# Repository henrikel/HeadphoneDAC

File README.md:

# HeadphoneDAC
This project started with the purchase of a couple of Chinese DAC modules designed around a PCM1794 DAC from TI. It turned out the DAC module was of quite good quality with genuine parts and a design closely following the datasheet reference design for the analog part. I therefore decided to make a headphone amplifier out of this with USB input. For this reason I had to design and construct the actual headphone amplifier as well as the logic that converts the USB data into an I2S stream that can be read by the DAC. A suitable power supply also had to be designed. All in all, the whole project therefore consists of 4 modules, one logic board with a STM32F411 running the show, one DAC module, one headphone amplifier module and one power supply.

The logic module takes care of converting the USB audio stream into I2S data on a USB full-speed interface. This sets a limit of the maximum sample rate to 96 kHz. It implements the proper way to handle the audio data, i.e., asynchronously. As of now, the system clock of the STM32 microcontroller is used for the audio clock, something that can be improved in the future. The STM32F411 microcontroller also takes care of the user interface, which consists of a few buttons and LEDs to indicate playback, mute and sampling rate. A LED VU meter is also implemented as well as control of a relay to avoid pops and clicks at startup and shutdown.

The headphone amplifier is a class A output design, using a NE5534 opamp as voltage amplifier and an emitter follower implemented as a Sziklai pair with a current sink. The design itself has borrowed from two sources, the Youtube channel Innove Workshop (but modified for dual supply) and Elliott Sound Products (https://sound-au.com/project113.htm). It is a relatively simple design, but measures well (I get THD figures of approximately 0.03% at 1 kHz and 100 mW, which is around the limit of my home made sound card using a Raspberry Pi and Hifiberry ADC+DAC). 

The power supply is a simple design giving +/-12 V and +5V, with a toroidal transformer and LM317/337 and L7812/7809/7805.

I am pretty happy with this build and think it sounds really good with my Beyerdynamic DT880 Pro headphones (250 ohms). I had some problems with ground loops and interference from the transformer in the case I built for the amplifier, but I think I have sorted out most of that now with some tweaking of the orientation of the transformer as well as appropriate grounding. What remains is an irritating high-pitched interference obviously coming from the digital parts of the controller module, which oddly enough can only be heard when muting the sound (if streaming is on, but no music is playing or very low levels of music, I can't hear it).

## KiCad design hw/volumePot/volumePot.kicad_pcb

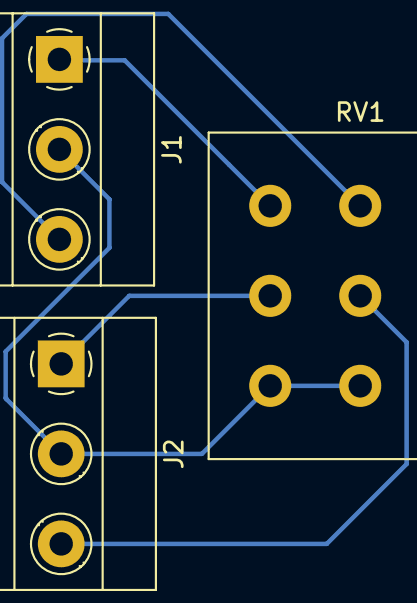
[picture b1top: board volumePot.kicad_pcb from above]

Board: 2 copper layers, 3 parts (0 on the bottom side), 5 nets.

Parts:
J1, J2: Screw_Terminal_01x03; TerminalBlock_Phoenix_MKDS-1,5-3_1x03_P5.00mm_Horizontal
RV1: R_POT_Dual; Potentiometer_Alps_RK163_Dual_Horizontal

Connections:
unnamed: J1.1, RV1.6
unnamed: J1.2, J2.2, RV1.1, RV1.4
unnamed: J1.3, RV1.3
unnamed: J2.1, RV1.5
unnamed: J2.3, RV1.2

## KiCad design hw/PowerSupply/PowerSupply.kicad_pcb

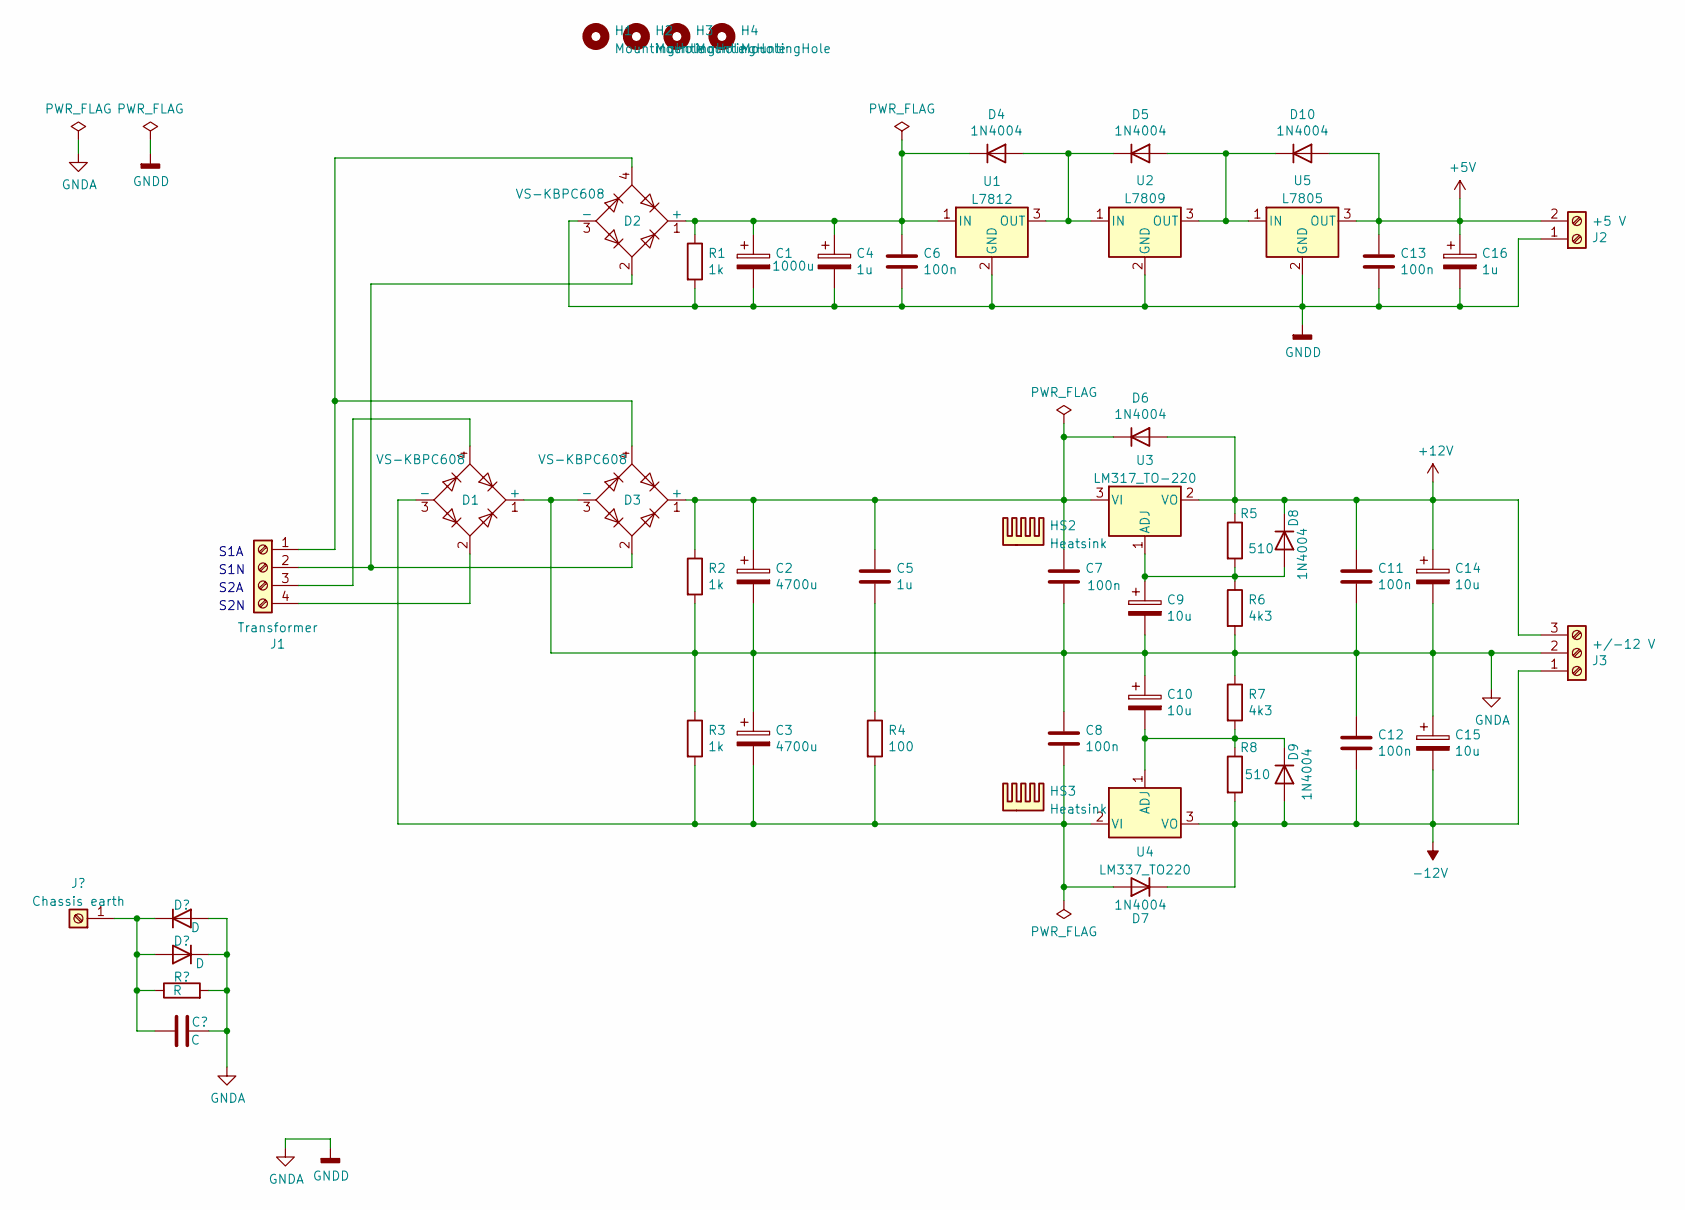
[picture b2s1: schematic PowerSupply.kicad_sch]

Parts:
C1: 1000u; CP_Radial_D18.0mm_P7.50mm
C2, C3: 4700u; CP_Radial_D18.0mm_P7.50mm
C4, C16: 1u; CP_Radial_D5.0mm_P2.00mm
C5: 1u; C_Rect_L7.0mm_W2.5mm_P5.00mm
C6, C7, C8, C11, C12, C13: 100n; C_Rect_L7.0mm_W2.5mm_P5.00mm
C9, C10, C14, C15: 10u; CP_Radial_D5.0mm_P2.00mm
D1, D2, D3: VS-KBPC608; Diode_Bridge_Vishay_KBPC6
D4, D5, D6, D7, D8, D9, D10: 1N4004; D_DO-41_SOD81_P10.16mm_Horizontal
H1, H2, H3, H4: MountingHole; MountingHole_3.2mm_M3
HS2, HS3: Heatsink; Heatsink_Fischer_SK104-STC-STIC_35x13mm_2xDrill2.5mm
J1: Transformer; TerminalBlock_Phoenix_MKDS-1,5-4_1x04_P5.00mm_Horizontal
J2: +5 V; TerminalBlock_Phoenix_MKDS-1,5-2_1x02_P5.00mm_Horizontal
J3: +/-12 V; TerminalBlock_Phoenix_MKDS-1,5-3_1x03_P5.00mm_Horizontal
R1, R2, R3: 1k; R_Axial_DIN0414_L11.9mm_D4.5mm_P20.32mm_Horizontal
R4: 100; R_Axial_DIN0207_L6.3mm_D2.5mm_P10.16mm_Horizontal
R5, R8: 510; R_Axial_DIN0207_L6.3mm_D2.5mm_P10.16mm_Horizontal
R6, R7: 4k3; R_Axial_DIN0207_L6.3mm_D2.5mm_P10.16mm_Horizontal
U1: L7812; TO-220-3_Vertical
U2: L7809; TO-220-3_Vertical
U3: LM317_TO-220; TO-220-3_Vertical
U4: LM337_TO220; TO-220-3_Vertical
U5: L7805; TO-220-3_Vertical

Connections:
+5V: C13.1, C16.1, D10.2 (A), J2.2, U5.3 (OUT)
+12V: C11.1, C14.1, D6.2 (A), D8.1 (K), J3.3, R5.1, U3.2 (VO)
-12V: C12.2, C15.2, D7.1 (K), D9.2 (A), J3.1, R8.2, U4.3 (VO)
GNDA: C1.2, C2.2, C3.1, C4.2, C6.2, C7.2, C8.1, C9.2, C10.1, C11.2, C12.1, C13.2, C14.2, C15.1, C16.2, D1.1 (+), D2.3 (-), D3.3 (-), J2.1, J3.2, R1.2, R2.2, R3.1, R6.2, R7.1, U1.2 (GND), U2.2 (GND), U5.2 (GND)
unnamed: C1.1, C4.1, C6.1, D2.1 (+), D4.1 (K), R1.1, U1.1 (IN)
unnamed: C2.1, C5.1, C7.1, D3.1 (+), D6.1 (K), R2.1, U3.3 (VI)
unnamed: C3.2, C8.2, D1.3 (-), D7.2 (A), R3.2, R4.2, U4.2 (VI)
unnamed: C5.2, R4.1
unnamed: C9.1, D8.2 (A), R5.2, R6.1, U3.1 (ADJ)
unnamed: C10.2, D9.1 (K), R7.2, R8.1, U4.1 (ADJ)
unnamed: D1.2, J1.4
unnamed: D1.4, J1.3
unnamed: D2.2, D3.2, J1.2
unnamed: D2.4, D3.4, J1.1
unnamed: D4.2 (A), D5.1 (K), U1.3 (OUT), U2.1 (IN)
unnamed: D5.2 (A), D10.1 (K), U2.3 (OUT), U5.1 (IN)

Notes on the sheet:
S1N
S2N
S2A
S1A

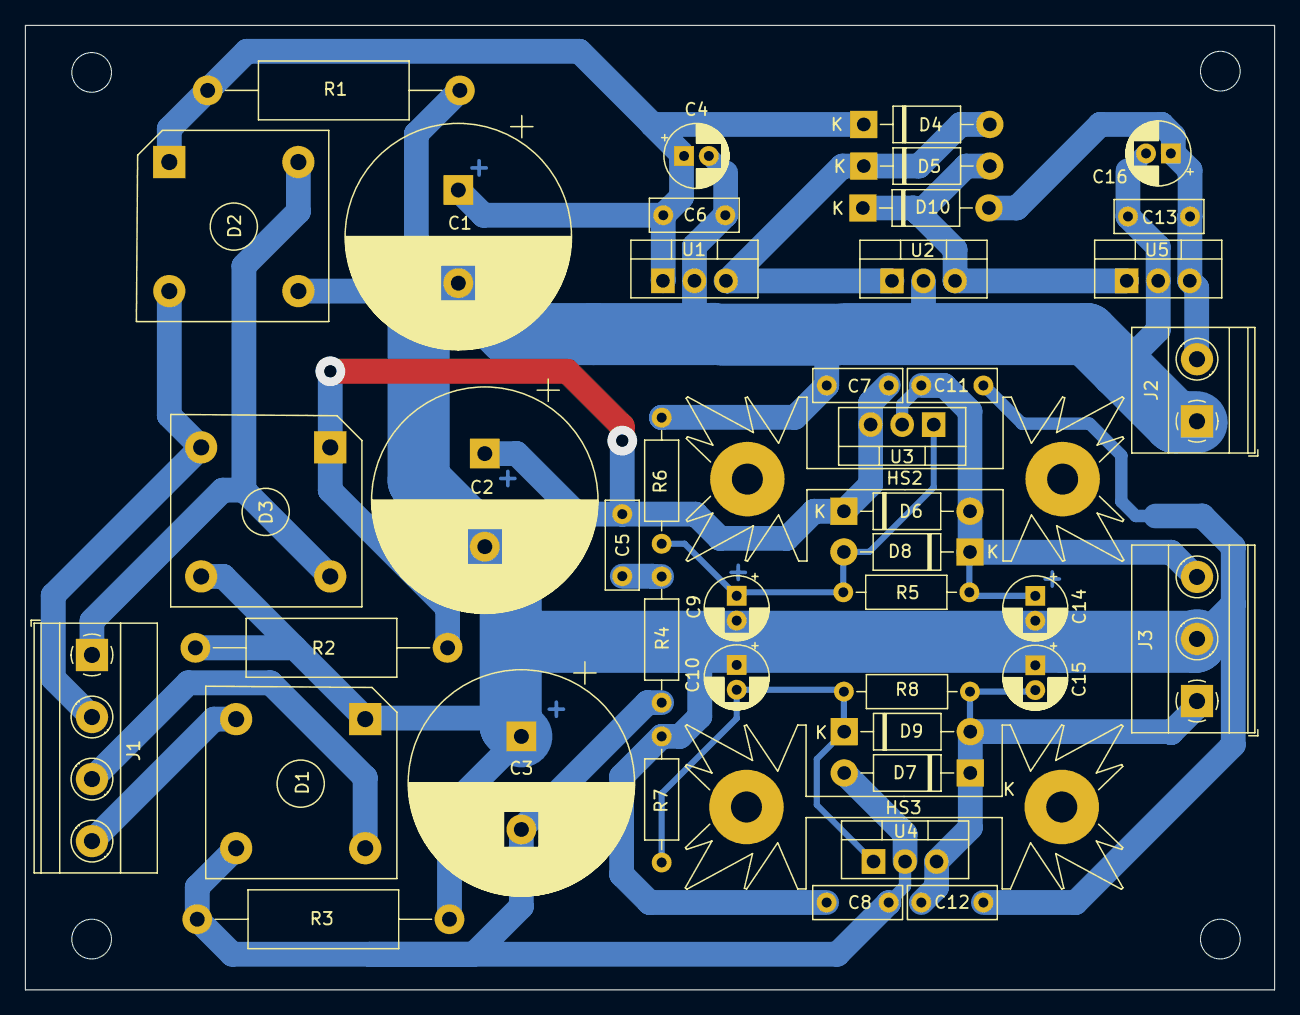
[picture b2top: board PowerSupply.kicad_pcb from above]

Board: 2 copper layers, 100.6 x 77.7 mm, 48 parts (0 on the bottom side), 16 nets.

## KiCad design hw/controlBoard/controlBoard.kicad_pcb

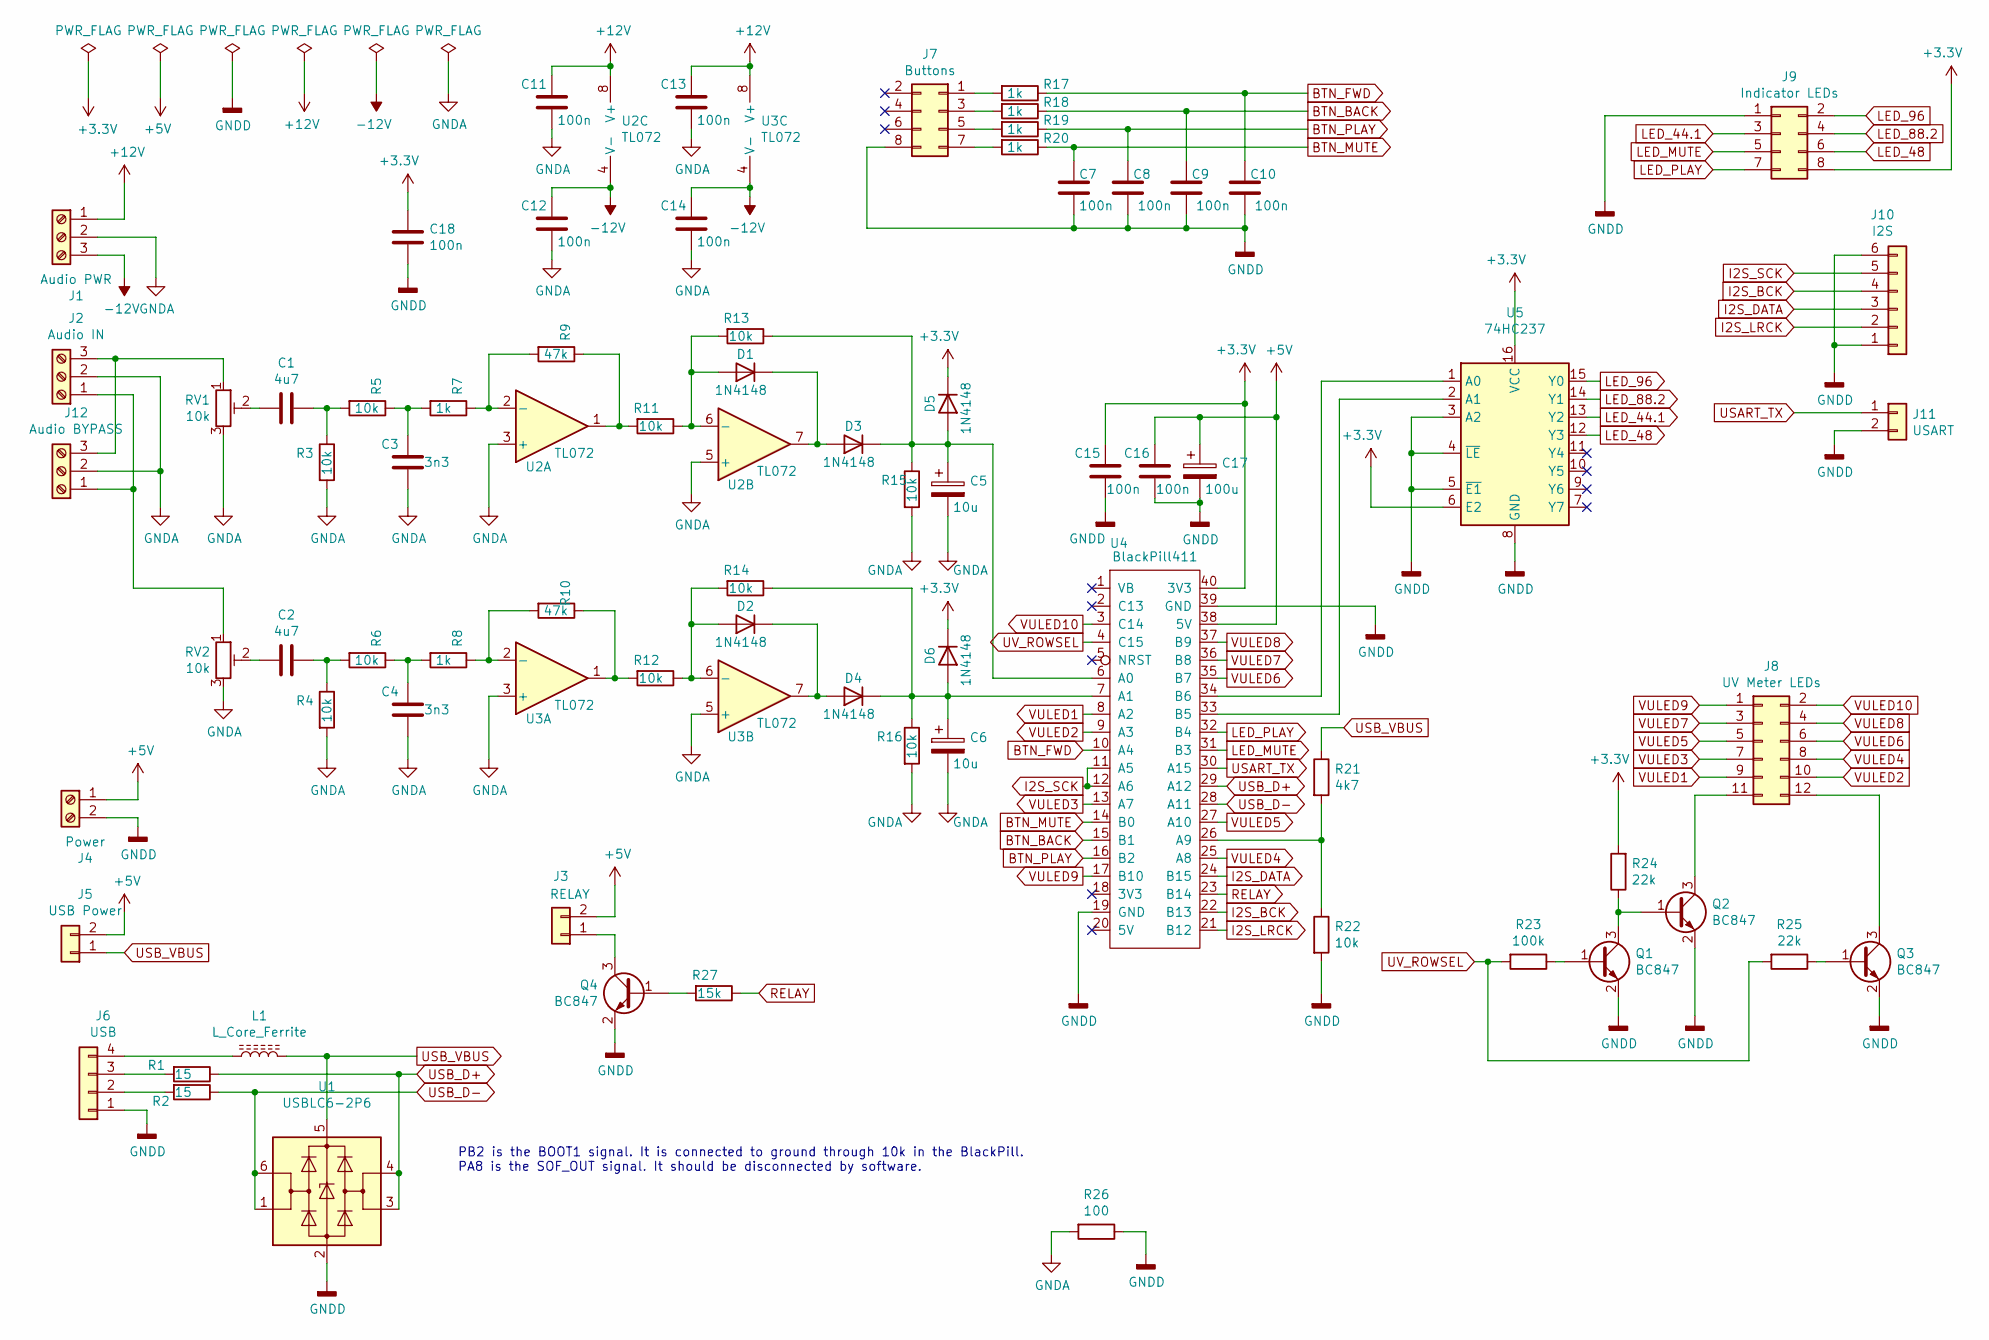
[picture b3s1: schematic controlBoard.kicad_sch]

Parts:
C1, C2: 4u7; C_0805_2012Metric_Pad1.18x1.45mm_HandSolder
C3, C4: 3n3; C_0805_2012Metric_Pad1.18x1.45mm_HandSolder
C5, C6: 10u; C_0805_2012Metric_Pad1.18x1.45mm_HandSolder
C7, C8, C9, C10, C11, C12, C13, C14, C15, C16, C18: 100n; C_0805_2012Metric_Pad1.18x1.45mm_HandSolder
C17: 100u; CP_Elec_6.3x5.4
D1, D2, D3, D4, D5, D6: 1N4148; D_SOD-323_HandSoldering
J1: Audio PWR; TerminalBlock_bornier-3_P5.08mm
J2: Audio IN; TerminalBlock_bornier-3_P5.08mm
J3: RELAY; PinHeader_1x02_P2.54mm_Vertical
J4: Power; TerminalBlock_bornier-2_P5.08mm
J5: USB Power; PinHeader_1x02_P2.54mm_Vertical
J6: USB; PinHeader_1x04_P2.54mm_Vertical
J7: Buttons; PinHeader_2x04_P2.54mm_Vertical
J8: UV Meter LEDs; PinHeader_2x06_P2.54mm_Vertical
J9: Indicator LEDs; PinHeader_2x04_P2.54mm_Vertical
J10: I2S; PinHeader_1x06_P2.54mm_Vertical
J11: USART; PinHeader_1x02_P2.54mm_Vertical
J12: Audio BYPASS; TerminalBlock_bornier-3_P5.08mm
L1: L_Core_Ferrite; L_Axial_L13.0mm_D4.5mm_P15.24mm_Horizontal_Fastron_HCCC
Q1, Q2, Q3, Q4: BC847; SOT-23
R1, R2: 15; R_0805_2012Metric_Pad1.20x1.40mm_HandSolder
R3, R4, R5, R6, R11, R12, R13, R14, R15, R16, R22: 10k; R_0805_2012Metric_Pad1.20x1.40mm_HandSolder
R7, R8: 1k; R_0805_2012Metric_Pad1.20x1.40mm_HandSolder
R9, R10: 47k; R_0805_2012Metric_Pad1.20x1.40mm_HandSolder
R17, R18, R19, R20: 1k; R_Axial_DIN0207_L6.3mm_D2.5mm_P10.16mm_Horizontal
R21: 4k7; R_0805_2012Metric_Pad1.20x1.40mm_HandSolder
R23: 100k; R_0805_2012Metric_Pad1.20x1.40mm_HandSolder
R24, R25: 22k; R_0805_2012Metric_Pad1.20x1.40mm_HandSolder
R26: 100; R_0805_2012Metric_Pad1.20x1.40mm_HandSolder
R27: 15k; R_0805_2012Metric_Pad1.20x1.40mm_HandSolder
RV1, RV2: 10k; Potentiometer_Piher_PT-10-V10_Vertical
U1: USBLC6-2P6; TSOT-23-6_HandSoldering
U2, U3: TL072; SO-8_3.9x4.9mm_P1.27mm
U4: BlackPill411
U5: 74HC237; DIP-16_W7.62mm_Socket_LongPads

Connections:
+3V3: C15.2, C18.1, D5.1 (K), D6.1 (K), J9.8, R24.2, U4.40 (3V3), U5.6 (E2), U5.16 (VCC)
+5V: C16.2, C17.1, J3.2, J4.1, J5.2, U4.38 (5V)
+12V: C11.2, C13.2, J1.1, U2.8 (V+), U3.8 (V+)
-12V: C12.2, C14.2, J1.3, U2.4 (V-), U3.4 (V-)
BTN_BACK: C9.1, R18.1, U4.15 (B1)
BTN_FWD: C10.1, R17.1, U4.10 (A4)
BTN_MUTE: C7.1, R20.1, U4.14 (B0)
BTN_PLAY: C8.1, R19.1, U4.16 (B2)
GNDA: C3.1, C4.1, C5.2, C6.2, C11.1, C12.1, C13.1, C14.1, J1.2, J2.2, J12.2, R3.2, R4.2, R15.2, R16.2, R26.2, RV1.3, RV2.3, U2.3 (+), U2.5 (+), U3.3 (+), U3.5 (+)
GNDD: C7.2, C8.2, C9.2, C10.2, C15.1, C16.1, C17.2, C18.2, J4.2, J6.1, J7.8, J9.1, J10.1, J10.6, J11.2, Q1.2 (E), Q2.2 (E), Q3.2 (E), Q4.2 (E), R22.2, R26.1, U1.2 (GND), U4.19 (GND), U4.39 (GND), U5.3 (A2), U5.4 (~LE), U5.5 (~E1), U5.8 (GND)
I2S_BCK: J10.4, U4.22 (B13)
I2S_DATA: J10.3, U4.24 (B15)
I2S_LRCK: J10.2, U4.21 (B12)
I2S_SCK: J10.5, U4.11 (A5), U4.12 (A6)
LED_44.1: J9.3, U5.13 (Y2)
LED_48: J9.6, U5.12 (Y3)
LED_88.2: J9.4, U5.14 (Y1)
LED_96: J9.2, U5.15 (Y0)
LED_MUTE: J9.5, U4.31 (B3)
LED_PLAY: J9.7, U4.32 (B4)
unnamed: C1.1, R3.1, R5.2
unnamed: C1.2, RV1.2
unnamed: C2.1, R4.1, R6.2
unnamed: C2.2, RV2.2
unnamed: C3.2, R5.1, R7.2
unnamed: C4.2, R6.1, R8.2
unnamed: C5.1, D3.1 (K), D5.2 (A), R13.1, R15.1, U4.6 (A0)
unnamed: C6.1, D4.1 (K), D6.2 (A), R14.1, R16.1, U4.7 (A1)
unnamed: D1.1 (K), D3.2 (A), U2.7
unnamed: D1.2 (A), R11.1, R13.2, U2.6 (-)
unnamed: D2.1 (K), D4.2 (A), U3.7
unnamed: D2.2 (A), R12.1, R14.2, U3.6 (-)
unnamed: J3.1, Q4.3 (C)
unnamed: J6.2, R2.2
unnamed: J6.3, R1.2
unnamed: J6.4, L1.1
unnamed: J7.1, R17.2
unnamed: J7.3, R18.2
unnamed: J7.5, R19.2
unnamed: J7.7, R20.2
unnamed: J8.11, Q2.3 (C)
unnamed: J8.12, Q3.3 (C)
unnamed: J2.1, J12.1, RV2.1
unnamed: J2.3, J12.3, RV1.1
unnamed: Q1.1 (B), R23.1
unnamed: Q1.3 (C), Q2.1 (B), R24.1
unnamed: Q3.1 (B), R25.1
unnamed: Q4.1 (B), R27.2
unnamed: R7.1, R9.2, U2.2 (-)
unnamed: R10.1, R12.2, U3.1
unnamed: R8.1, R10.2, U3.2 (-)
unnamed: R9.1, R11.2, U2.1
unnamed: R21.2, R22.1, U4.26 (A9)
unnamed: U4.33 (B5), U5.2 (A1)
unnamed: U4.34 (B6), U5.1 (A0)
RELAY: R27.1, U4.23 (B14)
USART_TX: J11.1, U4.30 (A15)
USB_D+: R1.1, U1.3 (I/O2), U1.4 (I/O2), U4.29 (A12)
USB_D-: R2.1, U1.1 (I/O1), U1.6 (I/O1), U4.28 (A11)
USB_VBUS: J5.1, L1.2, R21.1, U1.5 (VBUS)
UV_ROWSEL: R23.2, R25.2, U4.4 (C15)
VULED1: J8.9, U4.8 (A2)
VULED2: J8.10, U4.9 (A3)
VULED3: J8.7, U4.13 (A7)
VULED4: J8.8, U4.25 (A8)
VULED5: J8.5, U4.27 (A10)
VULED6: J8.6, U4.35 (B7)
VULED7: J8.3, U4.36 (B8)
VULED8: J8.4, U4.37 (B9)
VULED9: J8.1, U4.17 (B10)
VULED10: J8.2, U4.3 (C14)

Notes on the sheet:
PB2 is the BOOT1 signal. It is connected to ground through 10k in the BlackPill. PA8 is the SOF_OUT signal. It should be disconnected by software.

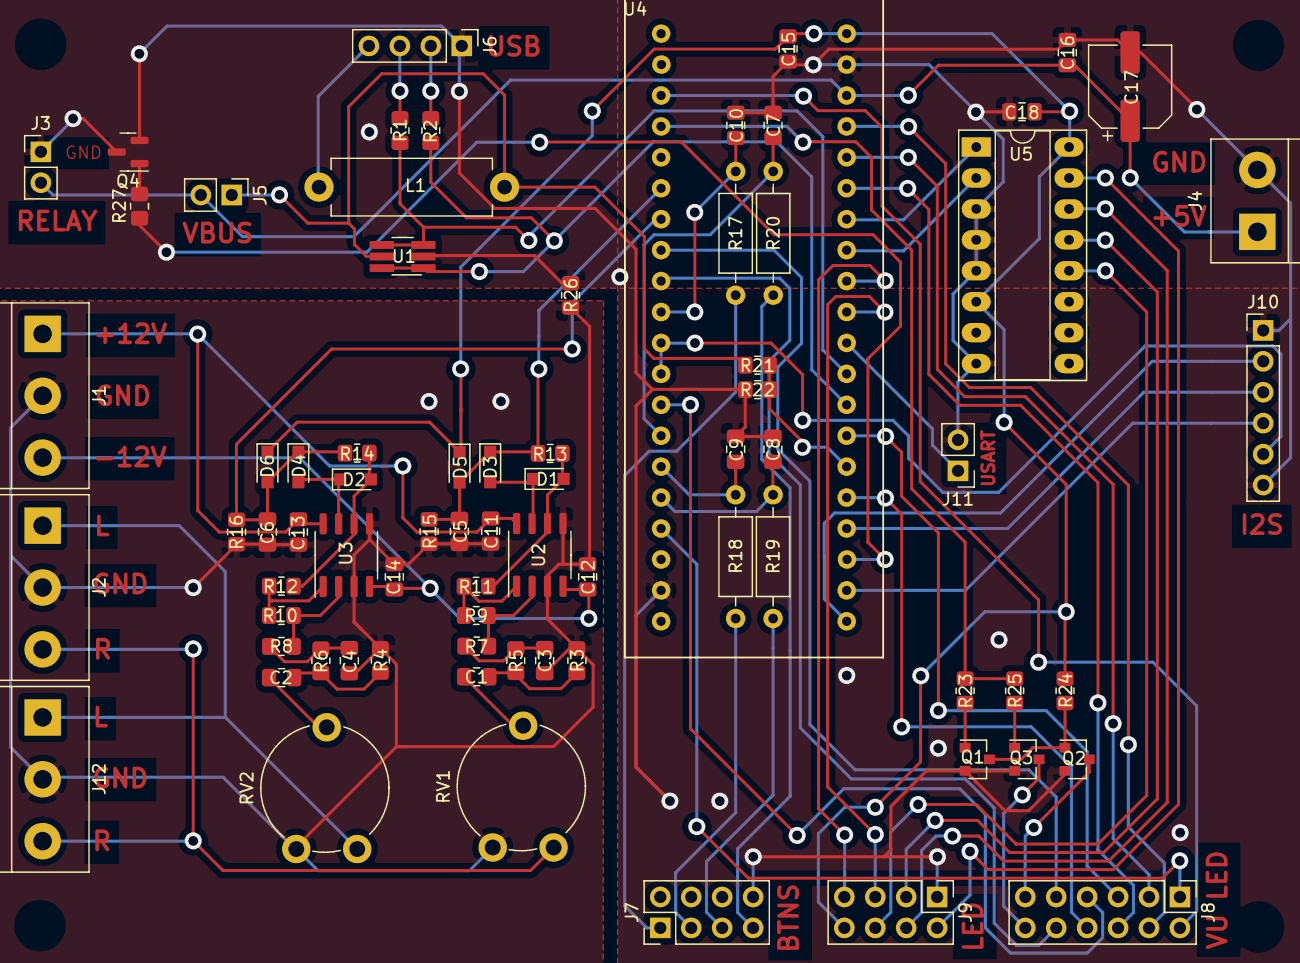
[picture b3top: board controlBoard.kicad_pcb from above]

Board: 2 copper layers, 75 parts (0 on the bottom side), 71 nets.

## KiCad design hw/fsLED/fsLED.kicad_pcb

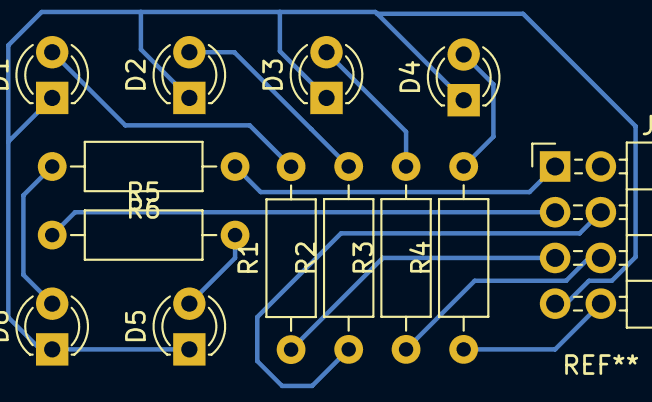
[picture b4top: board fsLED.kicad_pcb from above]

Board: 2 copper layers, 13 parts (0 on the bottom side), 13 nets.

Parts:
D1: 44.1; LED_D3.0mm
D2: 48; LED_D3.0mm
D3: 88.2; LED_D3.0mm
D4: 96; LED_D3.0mm
D5: MUTE; LED_D3.0mm
D6: PLAY; LED_D3.0mm
J1: Conn_02x04_Odd_Even; PinHeader_2x04_P2.54mm_Horizontal
R1, R2, R3, R4, R5, R6: R; R_Axial_DIN0207_L6.3mm_D2.5mm_P10.16mm_Horizontal

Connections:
44.1: J1.5, R1.1
48: J1.4, R2.1
88.2: J1.6, R3.1
96: J1.8, R4.1
GNDD: D1.1, D2.1, D3.1, D4.1, D5.1, D6.1, J1.7
MUTE: J1.3, R5.1
unnamed: D1.2, R1.2
unnamed: D2.2, R2.2
unnamed: D3.2, R3.2
unnamed: D4.2, R4.2
unnamed: D5.2, R5.2
unnamed: D6.2, R6.2
PLAY: J1.1, R6.1

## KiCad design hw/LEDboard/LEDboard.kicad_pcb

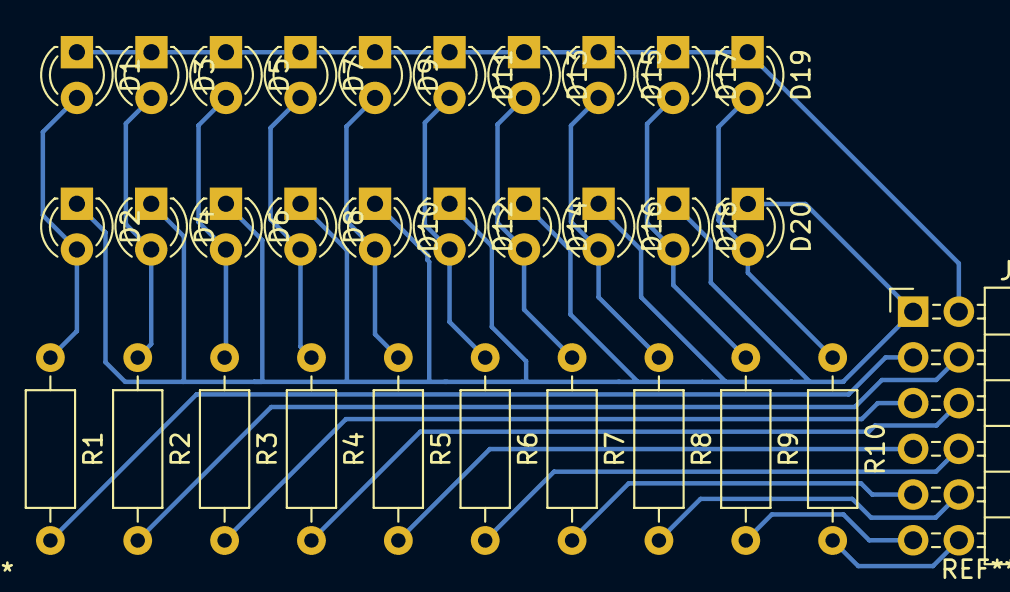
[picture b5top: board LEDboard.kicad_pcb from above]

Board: 2 copper layers, 31 parts (0 on the bottom side), 22 nets.

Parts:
D1, D2, D3, D4, D5, D6, D7, D8, D9, D10, D11, D12, D13, D14: G; LED_D3.0mm
D15, D16: Y; LED_D3.0mm
D17, D18, D19, D20: R; LED_D3.0mm
J1: Conn_02x06_Odd_Even; PinHeader_2x06_P2.54mm_Horizontal
R1, R2, R3, R4, R5, R6, R7: 270; R_Axial_DIN0207_L6.3mm_D2.5mm_P10.16mm_Horizontal
R8: 330; R_Axial_DIN0207_L6.3mm_D2.5mm_P10.16mm_Horizontal
R9, R10: 390; R_Axial_DIN0207_L6.3mm_D2.5mm_P10.16mm_Horizontal

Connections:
unnamed: D1.2, D2.2, R1.1
unnamed: D3.2, D4.2, R2.1
unnamed: D5.2, D6.2, R3.1
unnamed: D7.2, D8.2, R4.1
unnamed: D9.2, D10.2, R5.1
unnamed: D11.2, D12.2, R6.1
unnamed: D13.2, D14.2, R7.1
unnamed: D15.2, D16.2, R8.1
unnamed: D17.2, D18.2, R9.1
unnamed: D19.2, D20.2, R10.1
UVLED1: J1.3, R1.2
UVLED2: J1.4, R2.2
UVLED3: J1.5, R3.2
UVLED4: J1.6, R4.2
UVLED5: J1.7, R5.2
UVLED6: J1.8, R6.2
UVLED7: J1.9, R7.2
UVLED8: J1.10, R8.2
UVLED9: J1.11, R9.2
UVLED10: J1.12, R10.2
UVSEL1: D1.1, D3.1, D5.1, D7.1, D9.1, D11.1, D13.1, D15.1, D17.1, D19.1, J1.2
UVSEL2: D2.1, D4.1, D6.1, D8.1, D10.1, D12.1, D14.1, D16.1, D18.1, D20.1, J1.1

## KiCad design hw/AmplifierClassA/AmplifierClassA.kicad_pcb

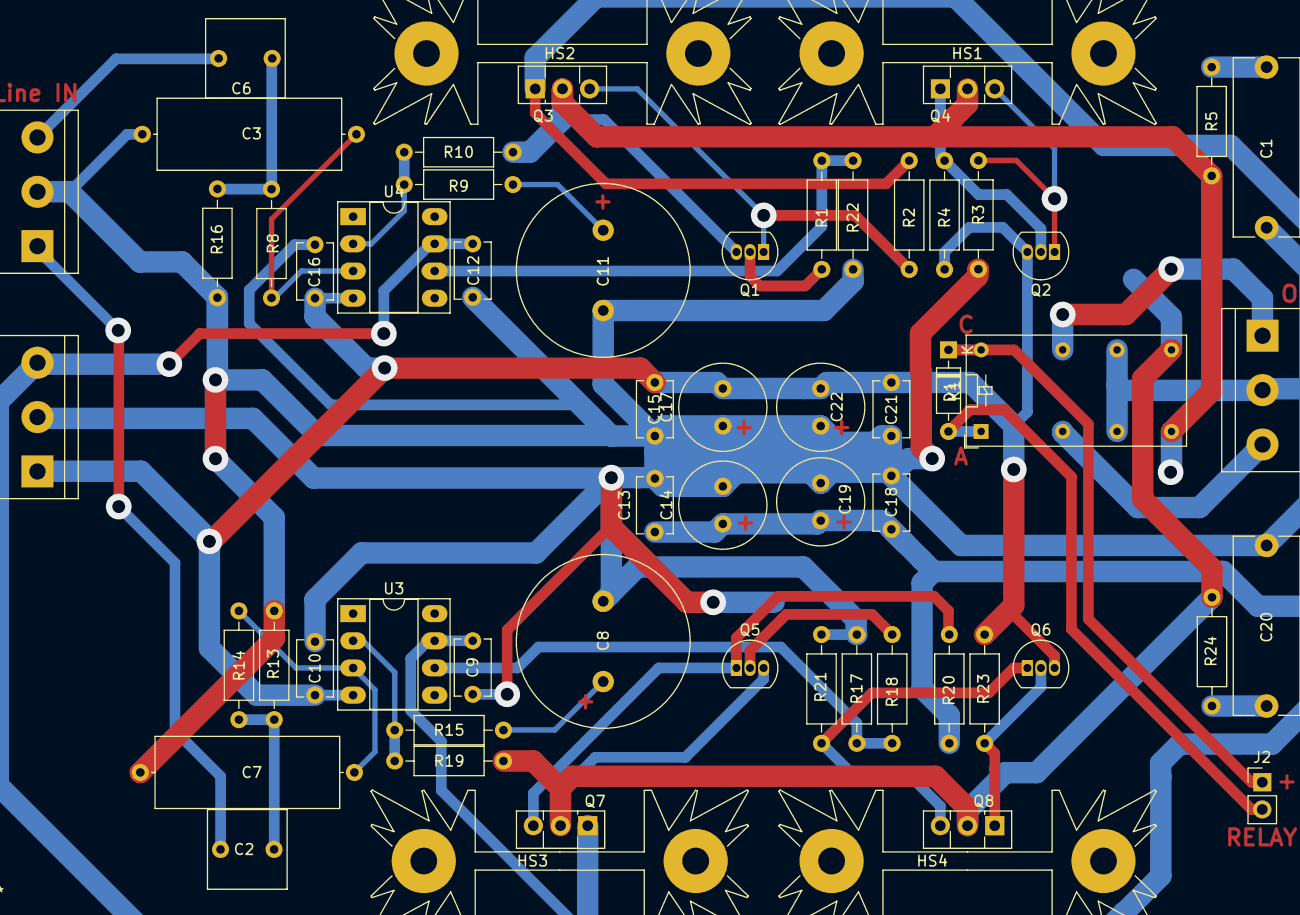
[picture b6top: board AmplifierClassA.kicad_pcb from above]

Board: 2 copper layers, 60 parts (0 on the bottom side), 31 nets.

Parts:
C1, C20: 0.1u; C_Rect_L16.5mm_W6.0mm_P15.00mm_MKT
C2, C6: 4u7; C_Rect_L7.2mm_W7.2mm_P5.00mm_FKS2_FKP2_MKS2_MKP2
C3, C7: 330p; C_Axial_L17.0mm_D6.5mm_P20.00mm_Horizontal
C8, C11: 100u; C_Radial_D16.0mm_H25.0mm_P7.50mm
C9, C10, C12, C13, C15, C16, C18, C21: 0.1u; C_Disc_D5.1mm_W3.2mm_P5.00mm
C14, C17, C19, C22: 100u; C_Radial_D8.0mm_H11.5mm_P3.50mm
D1: 1N4148; D_DO-35_SOD27_P7.62mm_Horizontal
HS1, HS2, HS3, HS4: Heatsink; Heatsink_Fischer_SK104-STC-STIC_35x13mm_2xDrill2.5mm
J1: Line IN; TerminalBlock_bornier-3_P5.08mm
J2: Relay; PinHeader_1x02_P2.54mm_Vertical
J4: Phones OUT; TerminalBlock_bornier-3_P5.08mm
J7: Power 12 V; TerminalBlock_bornier-3_P5.08mm
K1: EC2-3NU; Relay_DPDT_Omron_G5V-2
Q1, Q2, Q5, Q6: BC550; TO-92_Inline
Q3, Q7: BD140; TO-126-3_Vertical
Q4, Q8: BD139; TO-126-3_Vertical
R1, R18: 100; R_Axial_DIN0207_L6.3mm_D2.5mm_P10.16mm_Horizontal
R2, R8, R14, R20: 1k; R_Axial_DIN0207_L6.3mm_D2.5mm_P10.16mm_Horizontal
R3, R21: 4k7; R_Axial_DIN0207_L6.3mm_D2.5mm_P10.16mm_Horizontal
R4, R23: 5R6; R_Axial_DIN0207_L6.3mm_D2.5mm_P10.16mm_Horizontal
R5, R24: 10; R_Axial_DIN0207_L6.3mm_D2.5mm_P10.16mm_Horizontal
R9, R15: 3k; R_Axial_DIN0207_L6.3mm_D2.5mm_P10.16mm_Horizontal
R10, R13, R16, R17, R19, R22: 10k; R_Axial_DIN0207_L6.3mm_D2.5mm_P10.16mm_Horizontal
U3, U4: NE5534; DIP-8_W7.62mm_Socket_LongPads

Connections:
+12V: C9.1, C12.1, C13.1, C14.1, C18.1, C19.2, J7.3, Q3.1 (E), Q7.1 (E), R2.1, R20.1, U3.7 (V+), U4.7 (V+)
-12V: C10.1, C15.1, C16.1, C17.2, C21.1, C22.2, J7.1, Q2.3 (E), Q6.3 (E), R4.2, R23.2, U3.4 (V-), U4.4 (V-)
GNDA: C1.2, C3.1, C7.1, C8.2, C9.2, C10.2, C11.2, C12.2, C13.2, C14.2, C15.2, C16.2, C17.1, C18.2, C19.1, C20.2, C21.2, C22.1, J1.2, J4.2, J7.2, K1.6, K1.11, R3.1, R13.1, R16.1, R17.1, R21.1, R22.1
unnamed: C1.1, R5.2
unnamed: C2.1, R13.2, R14.1
unnamed: C2.2, J1.1
unnamed: C3.2, R8.2, U4.3 (+)
unnamed: C6.1, R8.1, R16.2
unnamed: C6.2, J1.3
unnamed: C7.2, R14.2, U3.3 (+)
unnamed: C8.1, R15.1
unnamed: C11.1, R9.1
unnamed: C20.1, R24.2
unnamed: D1.1 (K), J2.1, K1.16
unnamed: D1.2 (A), J2.2, K1.1
unnamed: J4.1, K1.13
unnamed: J4.3, K1.4
unnamed: K1.8, Q1.3 (E), Q3.2 (C), Q4.2 (C), R5.1, R10.1
unnamed: K1.9, Q5.3 (E), Q7.2 (C), Q8.2 (C), R19.1, R24.1
unnamed: Q1.1 (C), Q3.3 (B), R2.2
unnamed: Q1.2 (B), R1.1
unnamed: Q2.1 (C), Q4.3 (B), R3.2
unnamed: Q2.2 (B), Q4.1 (E), R4.1
unnamed: Q5.1 (C), Q7.3 (B), R20.2
unnamed: Q5.2 (B), R18.1
unnamed: Q6.1 (C), Q8.3 (B), R21.2
unnamed: Q6.2 (B), Q8.1 (E), R23.1
unnamed: R1.2, R22.2, U4.6
unnamed: R9.2, R10.2, U4.2 (-)
unnamed: R15.2, R19.2, U3.2 (-)
unnamed: R17.2, R18.2, U3.6

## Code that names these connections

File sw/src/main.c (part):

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	
	// Buttons
	// Button 1 (scan backward): PB1
	// Button 2 (Play/pause):    PB2
	// Button 3 (Scan forward):  PA4
	// Button 4 (Mute):          PB0
	GPIOA->MODER &= ~GPIO_MODER_MODER4;
	GPIOB->MODER &= ~GPIO_MODER_MODER0;
	GPIOB->MODER &= ~GPIO_MODER_MODER1;
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	GPIOB->PUPDR |= GPIO_PUPDR_PUPDR1_0;
	
	// LEDs
	// PB4: Play
	// PB3: Mute
	GPIOB->MODER &= ~GPIO_MODER_MODER3;
	GPIOB->MODER |= 1 << GPIO_MODER_MODER3_Pos;
	GPIOB->MODER &= ~GPIO_MODER_MODER4;
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	GPIOC->MODER &= ~GPIO_MODER_MODER15;
	GPIOC->MODER |= 1 << GPIO_MODER_MODER15_Pos;
	
	// RELAY pin
	// PB14
	GPIOB->MODER &= ~GPIO_MODER_MODER14;
	GPIOB->MODER |= 1 << GPIO_MODER_MODER14_Pos;
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
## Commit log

2022-07-25 Add code
2022-08-01 Added schematic images
2022-08-09 Added image
